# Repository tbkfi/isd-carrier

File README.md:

# Prototype PCB for International Sensor Development Project

This repository contains a schematic and pcb design for an international sensor development project between Metropolia UAS and Osnabrück Hochschule, which concluded on 2026.02.27.

## Board Features

The PCB provides 5V power to the MCU modules, which have built-in LDOs to provide 3V3 power
for external and integrated peripherals.

- Interleaved dual socket (BlackIoT Polverine and DFR1117)
- Built-in power switch (external reset/power button)
- LiPo protection circuit (2.4-4.2V)
- LiPo charging circuit (configurable output)
- Power Path management using P-FET, actuated by external power voltage to disconnect battery from load during charging.
- Auxiliary 3V3 output pin header.
- Multiple power input options (all selectively populatable):
	- JST(2.0mm): LiPo battery
	- JST(2.0mm): Photovoltaic panel (8-28V)
	- Header(2.54mm): E.g. Bench-top power supply
    - PCB USB-C (charging, 5V peripherals, main power)
	- (MCU module USB-C (no 5V peripherals, no charging!))
- Sensor support (for both Polverine & DFR1117):
	- BME690 via I2C (integrated, LGA, 3V3)
	- BMV080 via I2C (integrated, ZIF-connector, 3V3)*
	- Seeed E5 LoRa via UART (external, Grove, 3V3)
	- SPS30 via I2C (external, ZHR-5, 5V)
	- I2C (external, Grove, 3V3)
	- SPI (Header: CS, MISO, MOSI, SCK, GND)

## Documentation

See the repository directory labeled 'output' for the board revision files. The directory contains schematic (pdf), routing (png), and an interactive bill of materials (bom).

### Issues

This section contains issues encountered up to and during the final integration testing when using
this board with all the external peripherals. Some issues are PCB related, others are practical inefficiencies or overlooked details.

### version 0.1
1. ZIF-connector: Insertion direction is reversed. Causing the pin-direction to be flipped, making the connector unusable. Neccessitates the use of Polverine for BMV080 functionality.
2. Power Path: P-FET which was ordered had differing package type from original. Soldering was still possible at 45deg angle, and bending unneeded pins above the package to avoid shorts.
3. DW01A: Behaviour was unexpected during testing despite following datasheet application diagram in design. Couple workarounds were found, but ultimately the IC should be replaced in the design
with something more robust from TI or Microchip (E.g.) to increase reliability and control over the protection circuit.
4. Peripheral cabling: Operation was susceptible to jumpers, badly crimped or soldered cables, which caused unnecessary debugging and inconsistent results.
5. Prototype PCB count: Not enough prototypes were made to provide such large teams with an efficient number of PCBs while continuing to validate power management behaviour.
As LoRa and Sensor teams received one prototype, and found them to be in working condition, it became virtually impossible to get either of them back for more power-related validation. 
6. It's a good idea to validate the MCU modules and cabling that is in use by other teams, specially if they were made or modified by them, as on more than one ocassion incorrectly (or not at all)
soldered pin headers caused certain functionality to not work, as nothing was plugged in...
7. I2C Pull-ups: Existing 10k pulls caused issues with DFR1117, while the configuration worked with Polverine. The pull-ups on PCB were removed to fix the issue. Though it's possible
this issue was due to bad cabling or bad sensor, as the pull-ups shouldn't technically cause this kind of issue in this configuration.

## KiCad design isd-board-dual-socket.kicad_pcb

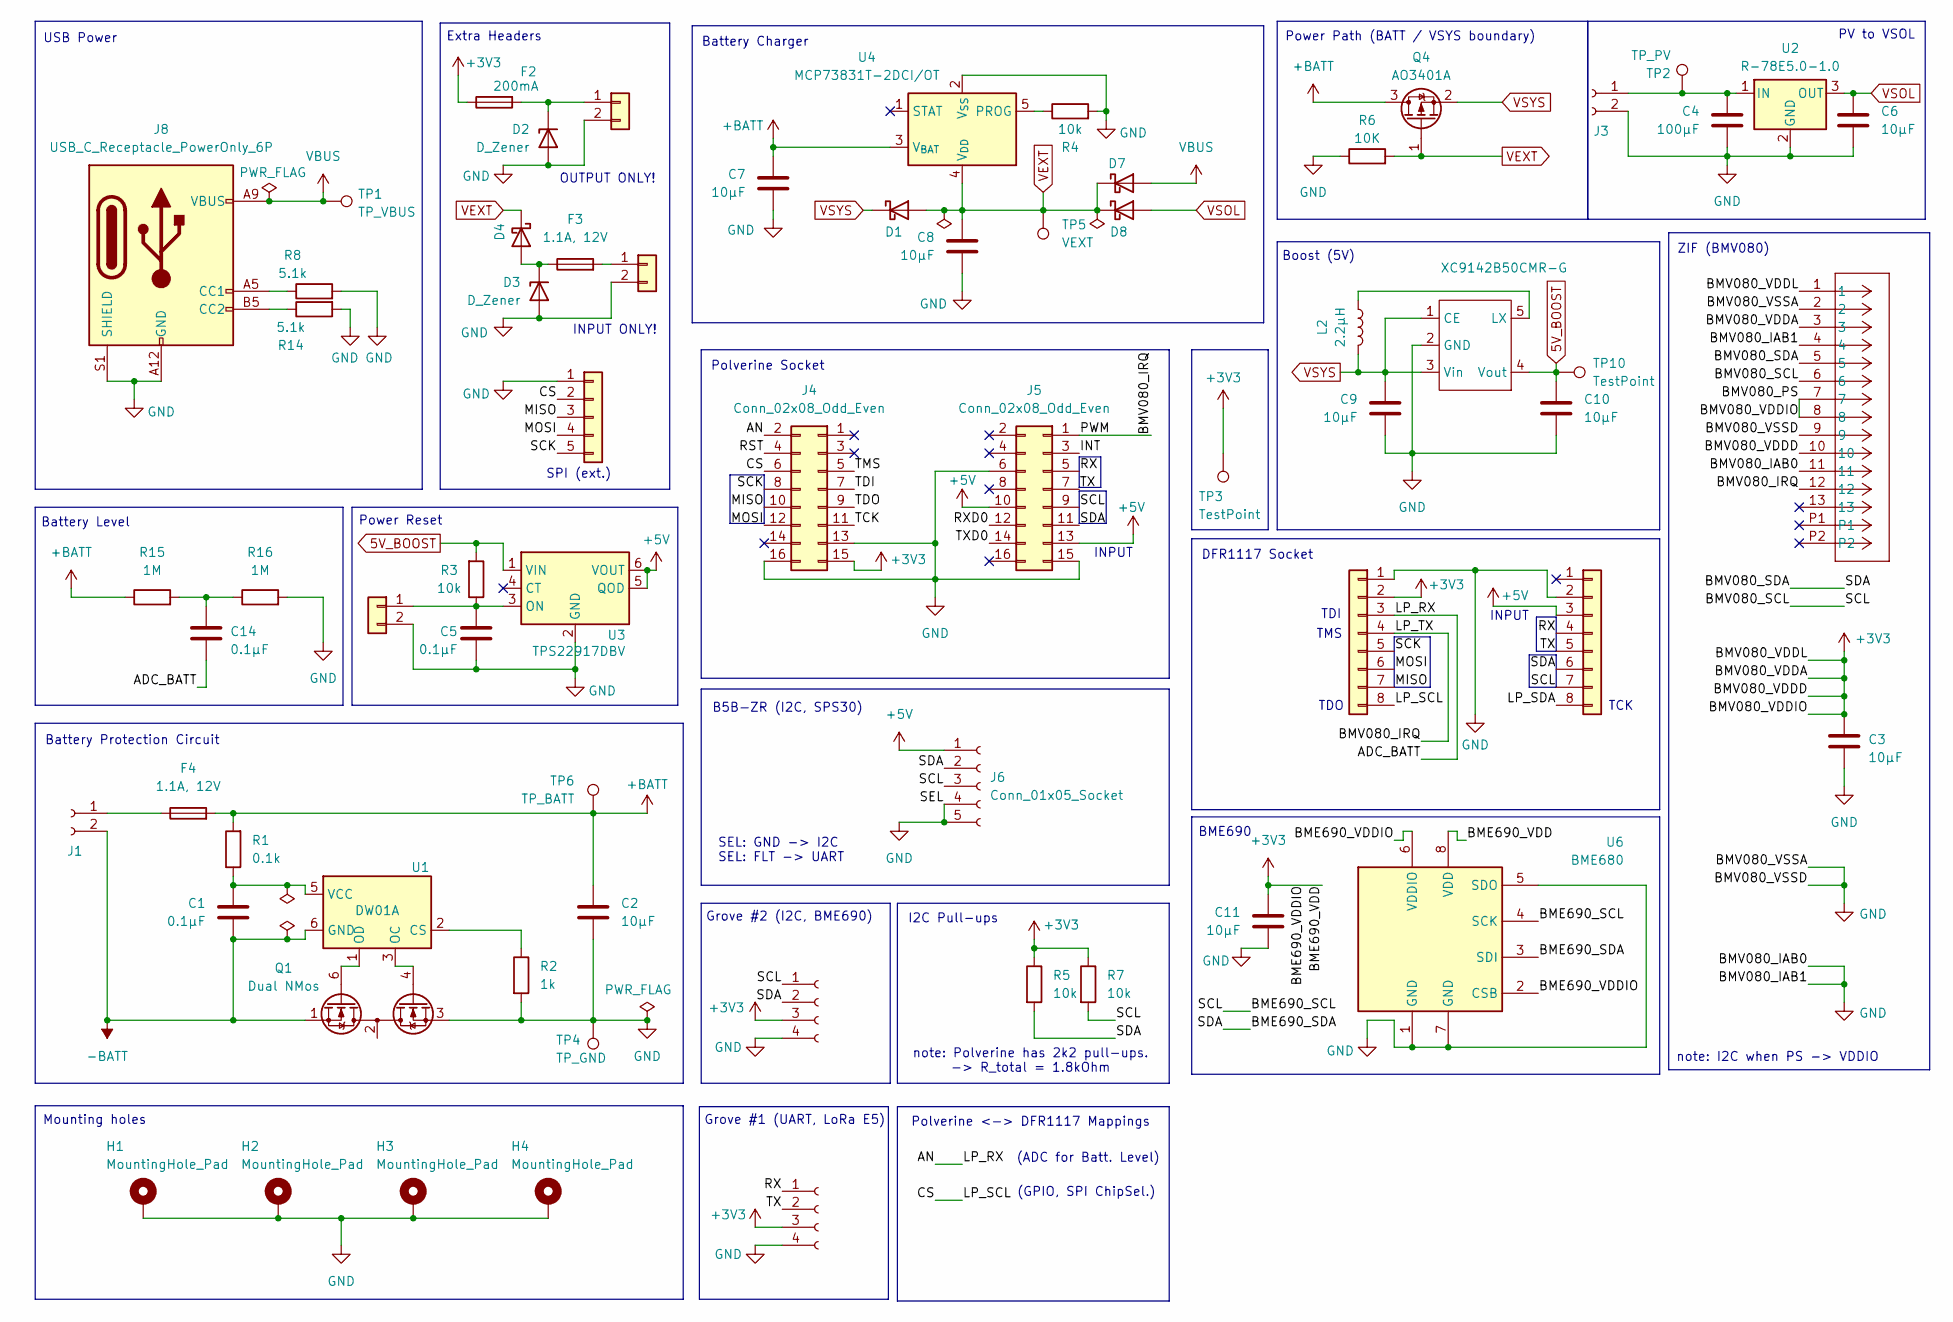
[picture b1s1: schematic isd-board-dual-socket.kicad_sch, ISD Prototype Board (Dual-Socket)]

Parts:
C1, C5, C14: 0.1µF; C_0805_2012Metric_Pad1.18x1.45mm_HandSolder; MPN 399-C0805C104K5RACTUCT-ND
C2, C3, C6, C7, C8, C9, C10, C11: 10µF; C_0805_2012Metric_Pad1.18x1.45mm_HandSolder; MPN GRM21BR61E106KA73K
C4: 100µF; C_Radial_D6.3mm_H11.0mm_P2.50mm; MPN RPF0608101M035K
D1, D4, D7, D8: D_Schottky; D_DO-41_SOD81_P10.16mm_Horizontal; MPN 1655-1N5817CT-ND
D2, D3: D_Zener; D_SOD-523; MPN CPDH5V0U
F2: 200mA; Fuse_0805_2012Metric_Pad1.15x1.40mm_HandSolder; MPN SMD0805B020TF
F3, F4: 1.1A, 12V; Fuse_1210_3225Metric_Pad1.42x2.65mm_HandSolder; MPN SMD1210B110TF
H1, H2, H3, H4: MountingHole_Pad; MountingHole_2.5mm_Pad_Via; MPN none
J1, J3: Conn_01x02_Socket; JST_PH_S2B-PH-K_1x02_P2.00mm_Horizontal; MPN 455-1719-ND
J2, J9: Conn_01x04_Socket; NS-Tech_Grove_1x04_P2mm_Vertical; MPN 1597-1082-ND
J4, J5: Conn_02x08_Odd_Even; PinSocket_2x08_P2.54mm_Vertical; MPN 732-61301621821-ND
J6: Conn_01x05_Socket; JST_ZH_B5B-ZR_1x05_P1.50mm_Vertical; MPN B5B-ZR
J7, J10: Conn_01x08; PinSocket_1x08_P2.54mm_Vertical; MPN PPTC081LFBN-RC
J8: USB_C_Receptacle_PowerOnly_6P; USB_C_Receptacle_GCT_USB4125-xx-x-0190_6P_TopMnt_Horizontal; MPN USB4125-GF-A
J12: 5035661302; CON_5035661302_MOL; MPN 046844713002846+
J13: Conn_01x05; PinHeader_1x05_P2.54mm_Vertical; MPN ???
J14, J15, J16: Conn_01x02; PinHeader_1x02_P2.54mm_Vertical; MPN 61300211121
L2: 2.2µH; L_Bourns-SRN4018; MPN SRN4018-2R2M
Q1: Dual NMos; SOT-23-6; MPN DMG9926UDMDICT-ND
Q4: AO3401A; SOT-23_Handsoldering; MPN AO3401A
R1: 0.1k; R_0805_2012Metric_Pad1.20x1.40mm_HandSolder; MPN 541-100CCT-ND
R2: 1k; R_0805_2012Metric_Pad1.20x1.40mm_HandSolder; MPN 10-ERJ-HP6J102VCT-ND
R3, R4, R5, R7: 10k; R_0805_2012Metric_Pad1.20x1.40mm_HandSolder; MPN 541-4163-1-ND
R6: 10K; R_0805_2012Metric_Pad1.20x1.40mm_HandSolder; MPN 541-4163-1-ND
R8, R14: 5.1k; R_0805_2012Metric_Pad1.20x1.40mm_HandSolder; MPN 311-5.1KARCT-ND
R15, R16: 1M; R_0805_2012Metric_Pad1.20x1.40mm_HandSolder; MPN 408-RG2012P-105-B-T5CT-ND
TP1: TP_VBUS; TestPoint_Pad_1.5x1.5mm; MPN none
TP2: TP_PV; TestPoint_Pad_1.5x1.5mm; MPN none
TP3, TP10: TestPoint; TestPoint_Pad_D1.0mm; MPN none
TP4: TP_GND; TestPoint_Pad_D1.0mm; MPN none
TP5: VEXT; TestPoint_Pad_1.5x1.5mm; MPN none
TP6: TP_BATT; TestPoint_Pad_1.5x1.5mm; MPN none
U1: DW01A; SOT-23-6_Handsoldering; MPN DW01A
U2: R-78E5.0-1.0; Converter_DCDC_RECOM_R-78E-0.5_THT; MPN R-78E5.0-1.0
U3: TPS22917DBV; SOT-23-6_Handsoldering; MPN TPS22917DBV
U4: MCP73831T-2DCI/OT; SOT-23-5_HandSoldering; MPN MCP73831T-2DCI/OT
U5: XC9142B50CMR-G; SOT-23-5_HandSoldering; MPN XC9142B50CMR-G
U6: BME680; Bosch_LGA-8_3x3mm_P0.8mm_ClockwisePinNumbering; MPN BME690

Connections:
5V_BOOST: C10.1, R3.2, TP10.1, U3.1 (VIN), U5.4 (Vout)
+3V3: C3.1, C11.1, F2.1, J2.3, J4.15, J9.3, J10.2, J12.1, J12.3, J12.7, J12.8, J12.10, R5.1, R7.1, TP3.1, U6.2 (CSB), U6.6 (VDDIO), U6.8 (VDD)
+5V: J5.10, J5.13, J6.1, J7.3, U3.5 (QOD), U3.6 (VOUT)
+BATT: C2.1, C7.1, F4.2, Q4.3 (D), R1.2, R15.1, TP6.1, U4.3 (V_{BAT})
-BATT: C1.2, J1.2, Q1.1 (D1), U1.6 (GND)
/ADC_BATT: C14.2, J4.2, J10.3
/BME690_SCL: J2.1, J5.9, J6.3, J7.7, J12.6, R7.2, U6.4 (SCK)
/BME690_SDA: J2.2, J5.11, J6.2, J7.6, J12.5, R5.2, U6.3 (SDI)
/BMV080_IRQ: J5.1, J10.4, J12.12
/CS: J4.6, J10.8, J13.2
/INT: J5.3
/LP_SDA: J7.8
/MISO: J4.10, J10.7, J13.3
/MOSI: J4.12, J10.6, J13.4
/RST: J4.4
/RX: J5.5, J7.4, J9.1
/RXD0: J5.12
/SCK: J4.8, J10.5, J13.5
/TCK: J4.11
/TDI: J4.7
/TDO: J4.9
/TMS: J4.5
/TX: J5.7, J7.5, J9.2
/TXD0: J5.14
GND: C2.2, C3.2, C4.2, C5.2, C6.2, C7.2, C8.2, C9.2, C10.2, C11.2, D2.2 (A), D3.2 (A), H1.1, H2.1, H3.1, H4.1, J2.4, J3.2, J4.13, J4.16, J5.6, J5.15, J6.4, J6.5, J7.2, J8.A12 (GND), J8.B12 (GND), J8.S1 (SHIELD), J9.4, J10.1, J12.2, J12.4, J12.9, J12.11, J13.1, J14.2, J15.2, J16.2, Q1.3 (S2), R2.2, R4.2, R6.1, R8.2, R14.2, R16.2, TP4.1, U2.2 (GND), U3.2 (GND), U4.2 (V_{SS}), U5.2 (GND), U6.1 (GND), U6.5 (SDO), U6.7 (GND)
unnamed: C14.1, R15.2, R16.1
unnamed: D2.1 (K), F2.2, J14.1
unnamed: D3.1 (K), D4.2 (A), F3.1
unnamed: F4.1, J1.1
unnamed: C4.1, J3.1, TP2.1, U2.1 (IN)
unnamed: J8.A5 (CC1), R8.1
unnamed: J8.B5 (CC2), R14.1
unnamed: F3.2, J15.1
unnamed: C5.1, J16.1, R3.1, U3.3 (ON)
unnamed: Q1.6 (G1), U1.1 (OD)
unnamed: Q1.4 (G2), U1.3 (OC)
unnamed: Q1.2 (S1/D2), Q1.5 (S1/D2)
unnamed: R2.1, U1.2 (CS)
unnamed: C1.1, R1.1, U1.5 (VCC)
unnamed: R4.1, U4.5 (PROG)
unnamed: L2.2, U5.5 (LX)
VBUS: D7.2 (A), J8.A9 (VBUS), J8.B9 (VBUS), TP1.1
VEXT: C8.1, D1.2 (A), D4.1 (K), D7.1 (K), D8.1 (K), Q4.1 (G), R6.2, TP5.1, U4.4 (V_{DD})
VSOL: C6.1, D8.2 (A), U2.3 (OUT)
VSYS: C9.1, D1.1 (K), L2.1, Q4.2 (S), U5.1 (CE), U5.3 (Vin)

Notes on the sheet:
INPUT
B5B-ZR (I2C, SPS30)
Polverine Socket
TDO
I2C Pull-ups
PV to VSOL
Battery Level
OUTPUT ONLY!
Power Reset
INPUT ONLY!
note: Polverine has 2k2 pull-ups. -> R_total = 1.8kOhm
DFR1117 Socket
Mounting holes
TDI
BME690
(GPIO, SPI ChipSel.)
Boost (5V)
TCK
Power Path (BATT / VSYS boundary)
Extra Headers
(ADC for Batt. Level)
Battery Charger
ZIF (BMV080)
Grove #1 (UART, LoRa E5)
SPI (ext.)
note: I2C when PS -> VDDIO
Battery Protection Circuit
Polverine <-> DFR1117 Mappings
TMS
USB Power
SEL: GND -> I2C SEL: FLT -> UART
Grove #2 (I2C, BME690)

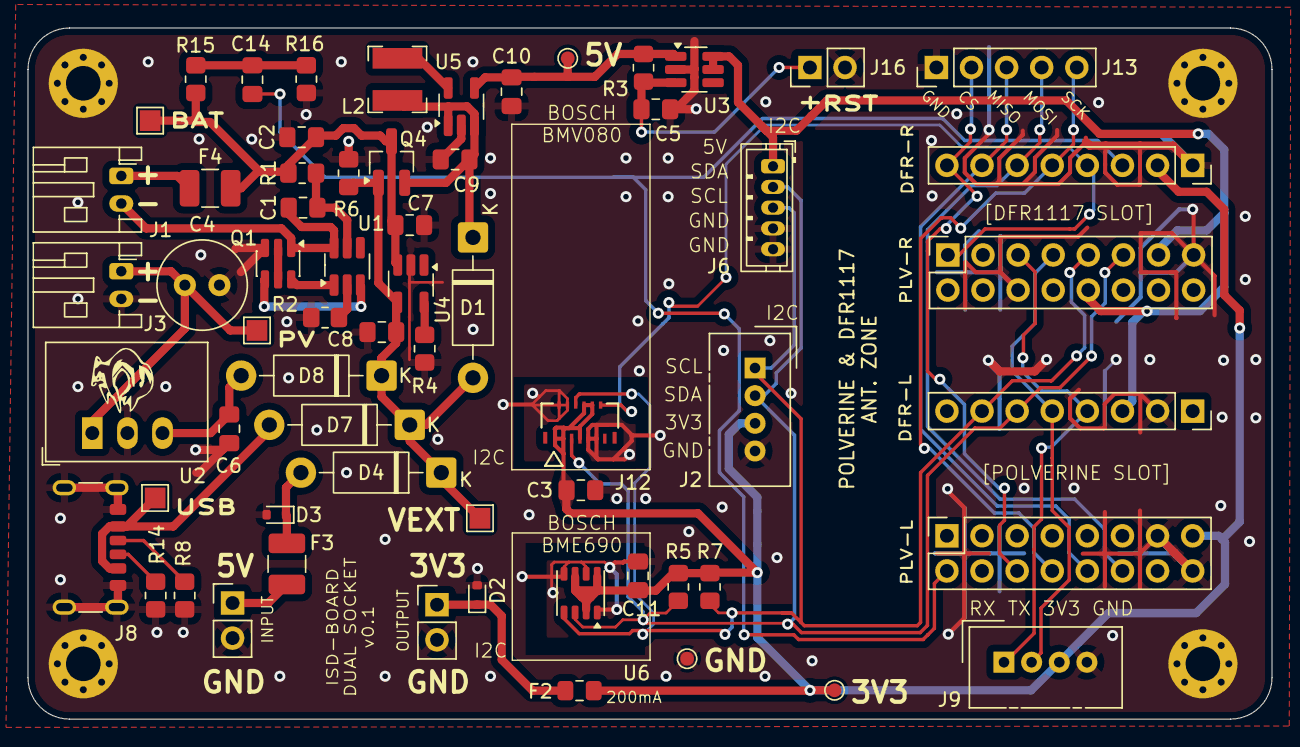
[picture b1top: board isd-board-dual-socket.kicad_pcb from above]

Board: 2 copper layers, 90.0 x 50.0 mm, 67 parts (0 on the bottom side), 36 nets.

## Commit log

2026-02-23 add: version 0.1
2026-02-23 add: v0.1/render.png
2026-02-23 update: README.md
2026-02-23 update: README.md (re-order)
2026-02-25 update: prototype image, track issues in README.md
2026-02-26 update: README.md (clarify v0.1 issues list)
2026-02-27 update: project conclusion
2026-02-27 update: README.md (fix indentation)
